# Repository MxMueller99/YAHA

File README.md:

# YAHA

**Y**et **A**nother **H**ome **A**ssistant is a small configurable ESP32 Application visualizing the current weather on a 1.69 Inch LCD Screen. 

## Showcase

## Requirements
- **ESP-IDF Version**		: 5.2.1
- **LVGL Version**			: 8.3.11
- 1.69 inch **LCD Screen** using ST7789v2
- **ESP32**

## Installation Instructions
1. Install the specified version of ESP-IDF.
2. Add LVGL as a dependency:
	- Option 1:  Install it directly via the ESP-IDF dependency management.
	- Option 2: Manually download LVGL component and place it in your ESP-IDF installation directory. For example, add it under:
`frameworks/esp-idf-v5.2.1/components/`

## Config

### Set your target (Recommended ESP32-S3)
`idf.py set-target esp32-s3`

### Config Settings
`idf.py menuconfig`

#### Partition Table
Partition Table -> Single factory app (large) 

#### LVGL
Component config -> LVGL configuration -> Font usage -> Enable built-in Fonts -> Enable Montserrat 14 & 30

#### Wifi Config
WiFi Configuration -> WiFi SSID
WiFi Configuration -> WiFi Password

#### Openweather Config
API Configuration -> OpenWeatherAPI Key
API Configuration -> OpenWeather City

## Building & Flashing
After configuring the Environment you can start building:\
`idf.py build`

And flashing:\
`idf.py flash`

For debugging:\
`idf.py monitor`

## PCB
For a more slick design we also designed a custom PCB in KiCad, which integrates the LCD perfectly with the ESP32-S3. Four M2 screw holes perfectly fit with the [Waveshare LCD-module](https://www.waveshare.com/1.69inch-lcd-module.htm) for easy assembly. The files can be found under
 `/assets/pcb/`

### PCB Showcase

## License
This project is licensed under the MIT License. See the [LICENSE]() file for details.

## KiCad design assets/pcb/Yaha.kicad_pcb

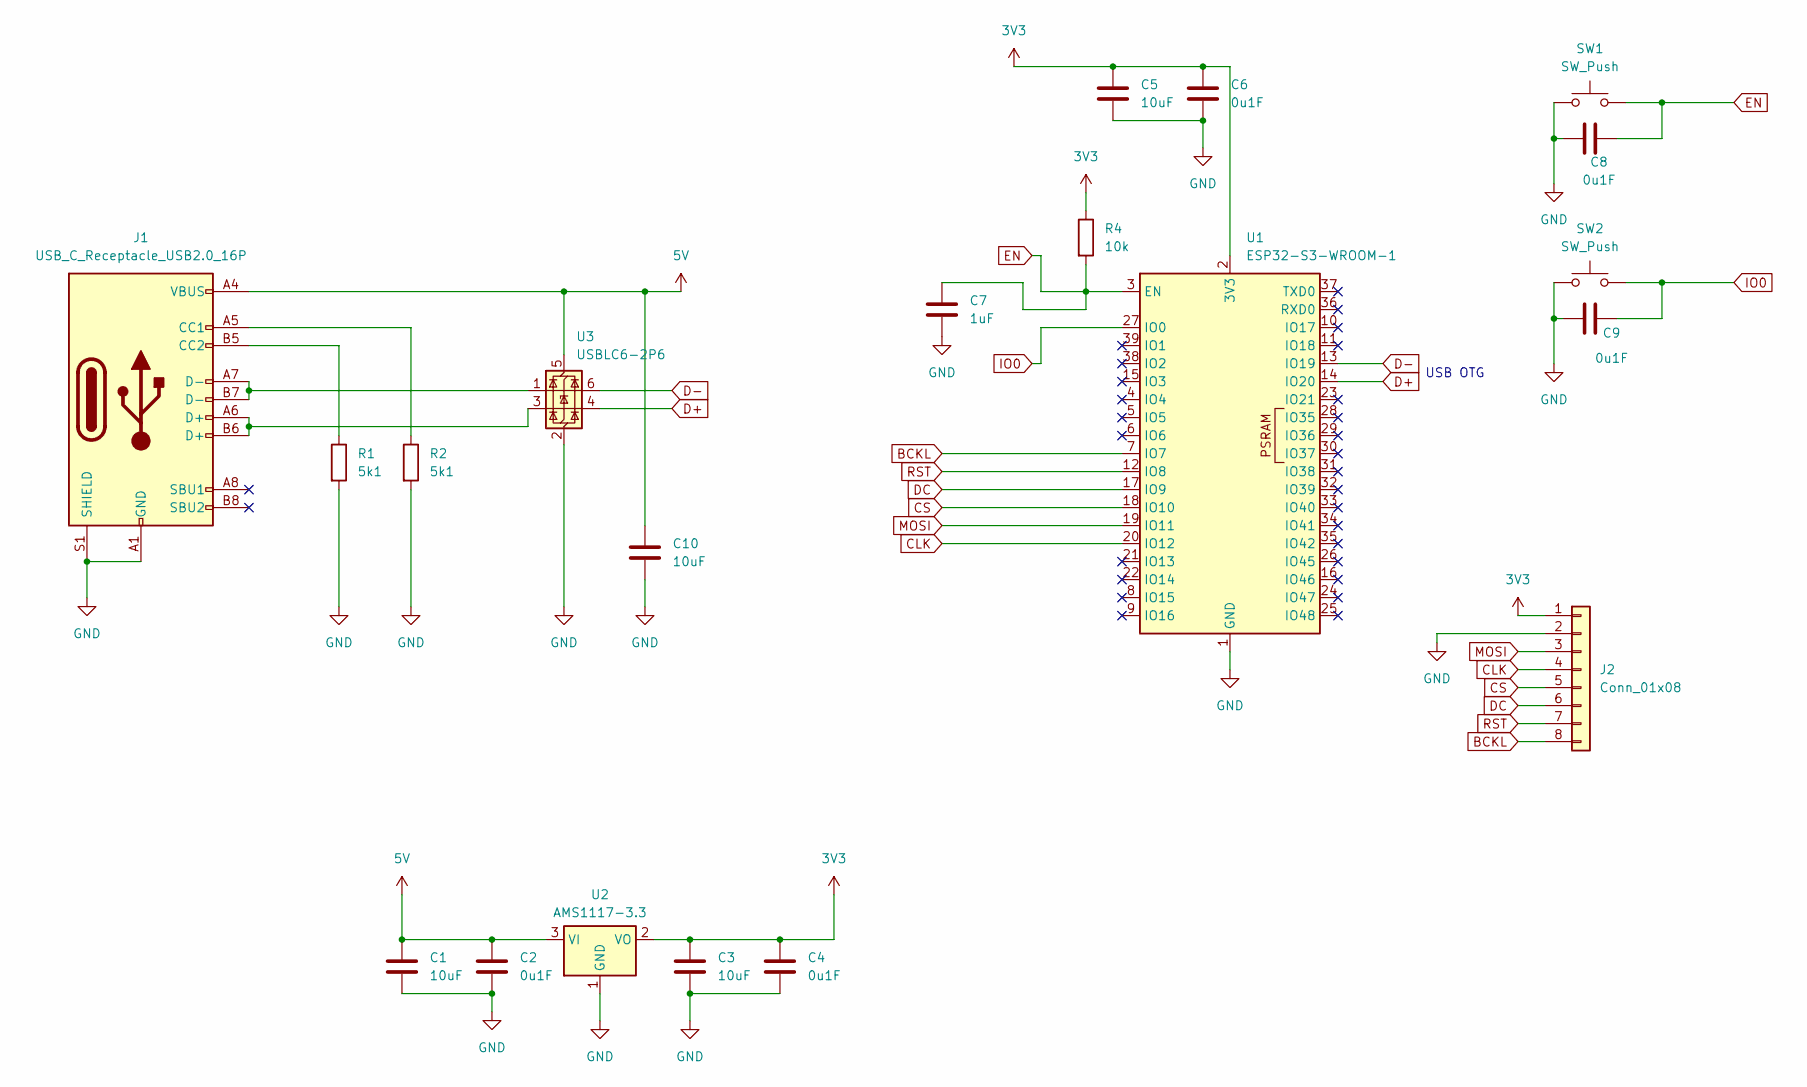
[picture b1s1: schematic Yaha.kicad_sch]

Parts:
C1, C3, C5, C10: 10uF; C_0603_1608Metric
C2, C4, C6, C8, C9: 0u1F; C_0603_1608Metric
C7: 1uF; C_0603_1608Metric
J1: USB_C_Receptacle_USB2.0_16P; USB_C_Receptacle_GCT_USB4105-xx-A_16P_TopMnt_Horizontal
J2: Conn_01x08; Molex_LCD_conn
R1, R2: 5k1; R_0603_1608Metric
R4: 10k; R_0603_1608Metric
SW1, SW2: SW_Push; SW_SPST_PTS810
U1: ESP32-S3-WROOM-1
U2: AMS1117-3.3; SOT-223-3_TabPin2
U3: USBLC6-2P6; SOT-666

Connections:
3V3: C3.1, C4.1, C5.1, C6.1, J2.1, R4.1, U1.2 (3V3), U2.2 (VO)
5V: C1.1, C2.1, C10.1, J1.A4 (VBUS), J1.A9 (VBUS), J1.B4 (VBUS), J1.B9 (VBUS), U2.3 (VI), U3.5 (VBUS)
BCKL: J2.8, U1.7 (IO7)
CLK: J2.4, U1.20 (IO12)
CS: J2.5, U1.18 (IO10)
D+: U1.14 (IO20), U3.4 (I/O2)
D-: U1.13 (IO19), U3.6 (I/O1)
DC: J2.6, U1.17 (IO9)
EN: C7.1, C8.2, R4.2, SW1.2, U1.3 (EN)
GND: C1.2, C2.2, C3.2, C4.2, C5.2, C6.2, C7.2, C8.1, C9.1, C10.2, J1.A1 (GND), J1.A12 (GND), J1.B1 (GND), J1.B12 (GND), J1.S1 (SHIELD), J2.2, R1.2, R2.2, SW1.1, SW2.1, U1.1 (GND), U1.40 (GND), U1.41 (GND), U2.1 (GND), U3.2 (GND)
IO0: C9.2, SW2.2, U1.27 (IO0)
MOSI: J2.3, U1.19 (IO11)
unnamed: J1.A5 (CC1), R2.1
unnamed: J1.B5 (CC2), R1.1
unnamed: J1.A6 (D+), J1.B6 (D+), U3.3 (I/O2)
unnamed: J1.A7 (D-), J1.B7 (D-), U3.1 (I/O1)
RST: J2.7, U1.12 (IO8)

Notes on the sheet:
USB OTG

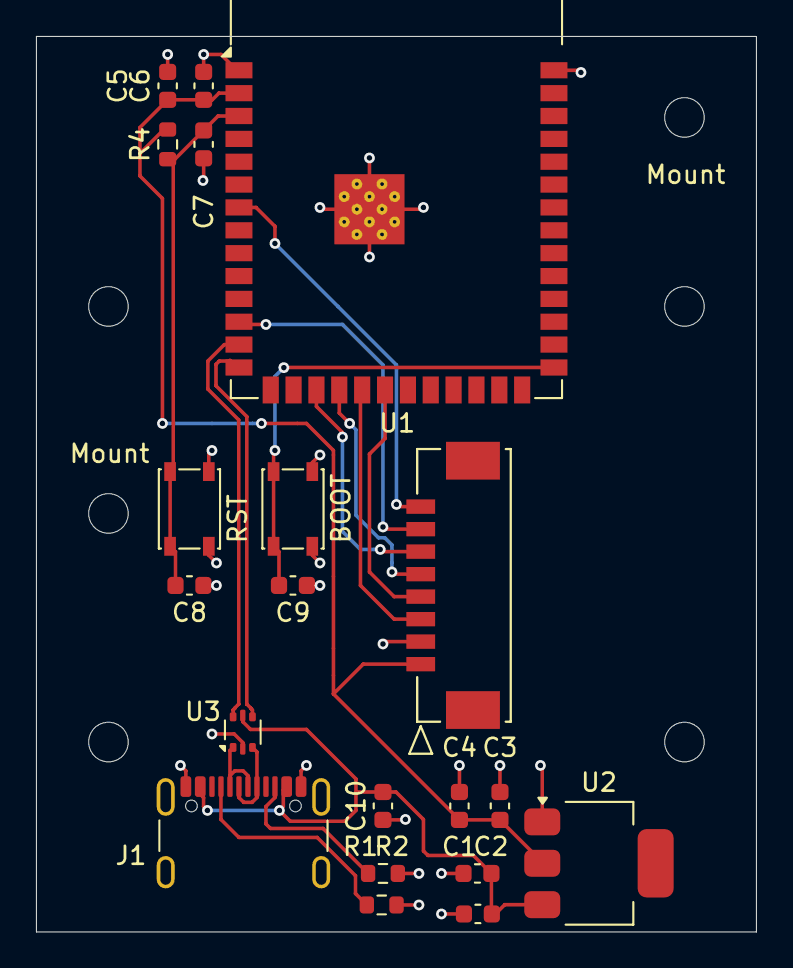
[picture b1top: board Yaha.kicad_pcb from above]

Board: 2 copper layers, 40.0 x 49.8 mm, 20 parts (0 on the bottom side), 17 nets.

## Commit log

2024-03-10 Initial Push
2024-03-10 test commit
2024-03-10 Added WiFi Functionality
2024-03-10 Weather API Call
2024-03-10 Inetgration of basic display functionality
2024-03-10 Included Waveshare LCD Datasheet
2024-03-10 Added ISR for screen switching
2024-03-10 Notation changes
2024-03-10 displayScreen1()
2024-03-10 Screen switching via button implemented
2024-03-30 Newly implemented Bitcoin and changed to eSPI LIB
2024-03-30 Major changes to API Call
2024-03-30 Major Changes to API Calls
2024-03-30 Added .gitignore for config
2024-03-30 Restored config.h
2024-08-14 Integration of ESP IDF
2025-05-23 Polished YAHA
2025-05-23 Create LICENSE
